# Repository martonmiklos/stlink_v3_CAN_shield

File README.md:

# STLink-v3 CAN breakout board

Replacement board for the MB1440 to expose the CAN bridge through an MCP2562-E/SN transciver to a DSUB connector

Drawn in Autodesk EAGLE 9.x

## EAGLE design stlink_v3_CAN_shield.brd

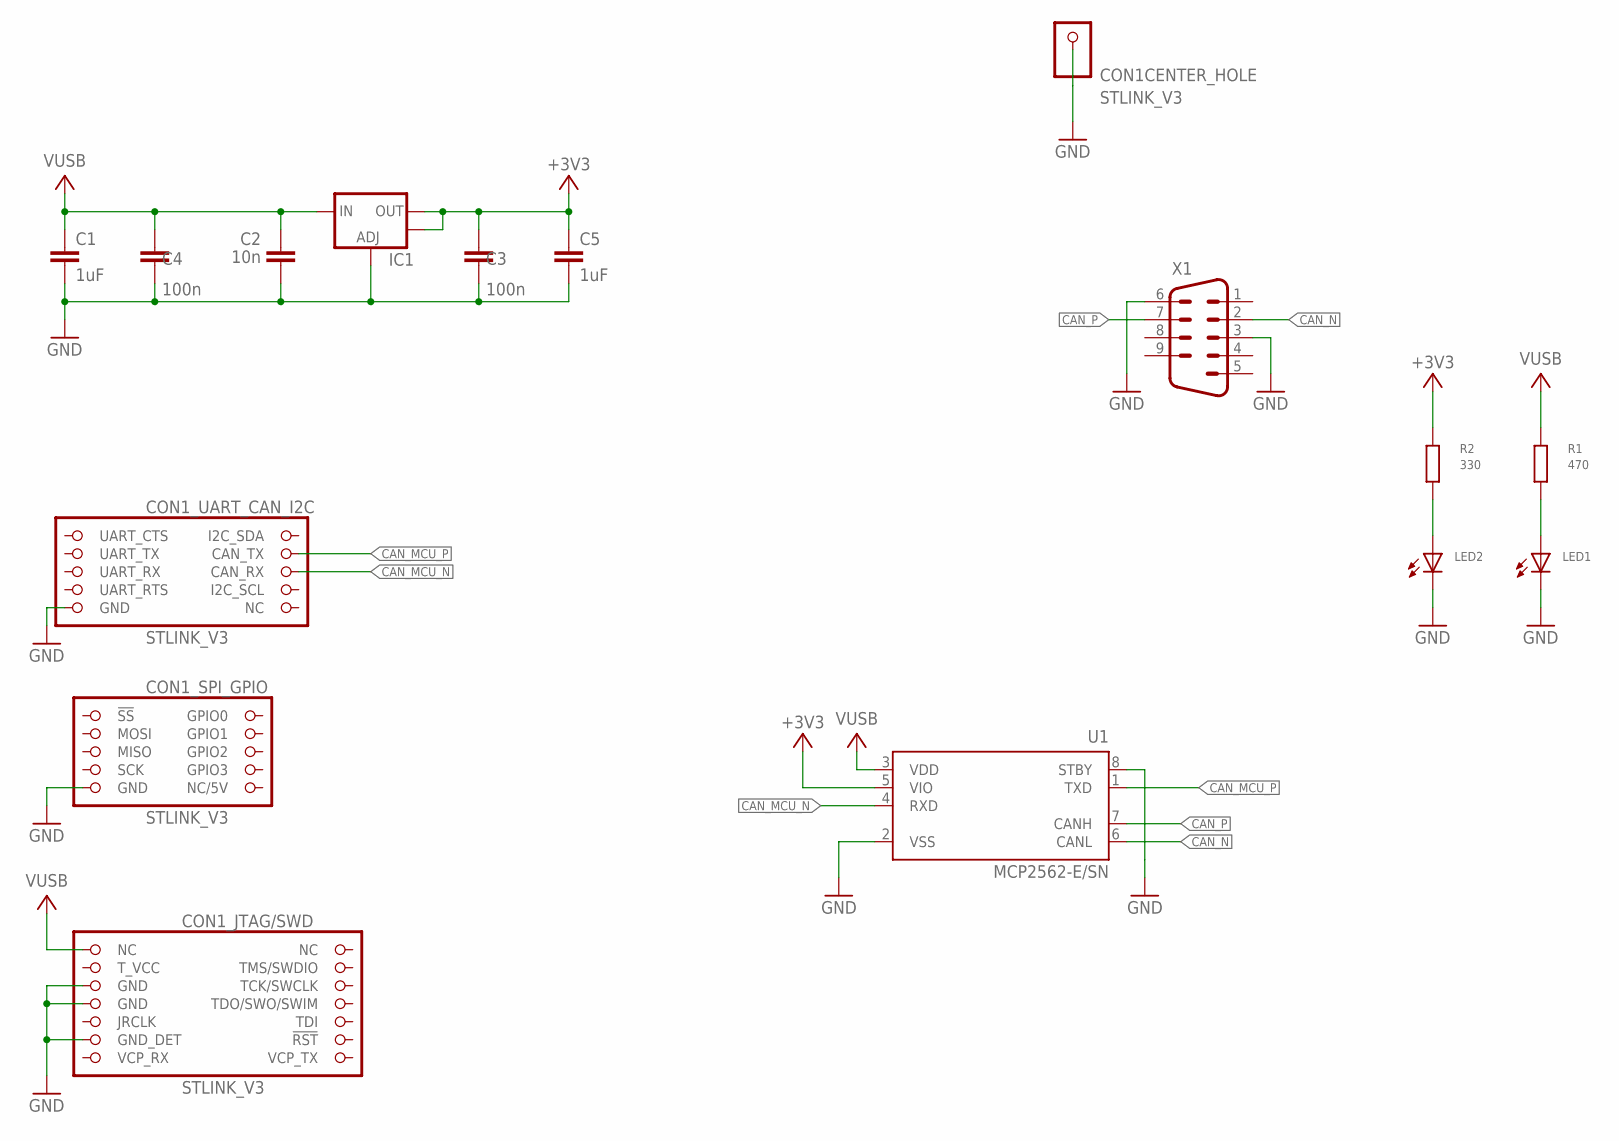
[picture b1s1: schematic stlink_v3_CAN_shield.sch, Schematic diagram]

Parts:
C1, C5: 1uF; C0603
C2: 10n; C0603
C3, C4: 100n; C0603
CON1: STLINK_V3; STLINKV3_HAT_NO_CONTOUR
IC1: V_REG_LM1117SOT223; SOT223
LED1, LED2: LED-0603; LED-603
R1: 470; R0603
R2: 330; R0603
U1: MCP2562-E/SN; SOIC127P600X175-8N
X1: M09H

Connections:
+3V3: C3.2, C5.1, IC1.2 (OUT), IC1.4 (OUT), R2.1, U1.5 (VIO)
CAN_MCU_N: CON1.UART_6 (CAN_RX), U1.4 (RXD)
CAN_MCU_P: CON1.UART_4 (CAN_TX), U1.1 (TXD)
CAN_N: U1.6 (CANL), X1.2
CAN_P: U1.7 (CANH), X1.7
GND: C1.2, C2.2, C3.1, C4.1, C5.2, CON1.CENTER (1), CON1.SPI_9 (GND), CON1.STDC_14_5 (GND), CON1.STDC_14_7 (GND), CON1.STDC_14_11 (GND_DET), CON1.UART_9 (GND), IC1.1 (ADJ), LED1.C, LED2.C, U1.2 (VSS), U1.8 (STBY), X1.3, X1.6
VIN_LED_R1: LED2.A, R2.2
VIN_LED_R2: LED1.A, R1.2
VUSB: C1.1, C2.1, C4.2, CON1.STDC_14_1 (NC), IC1.3 (IN), R1.1, U1.3 (VDD)

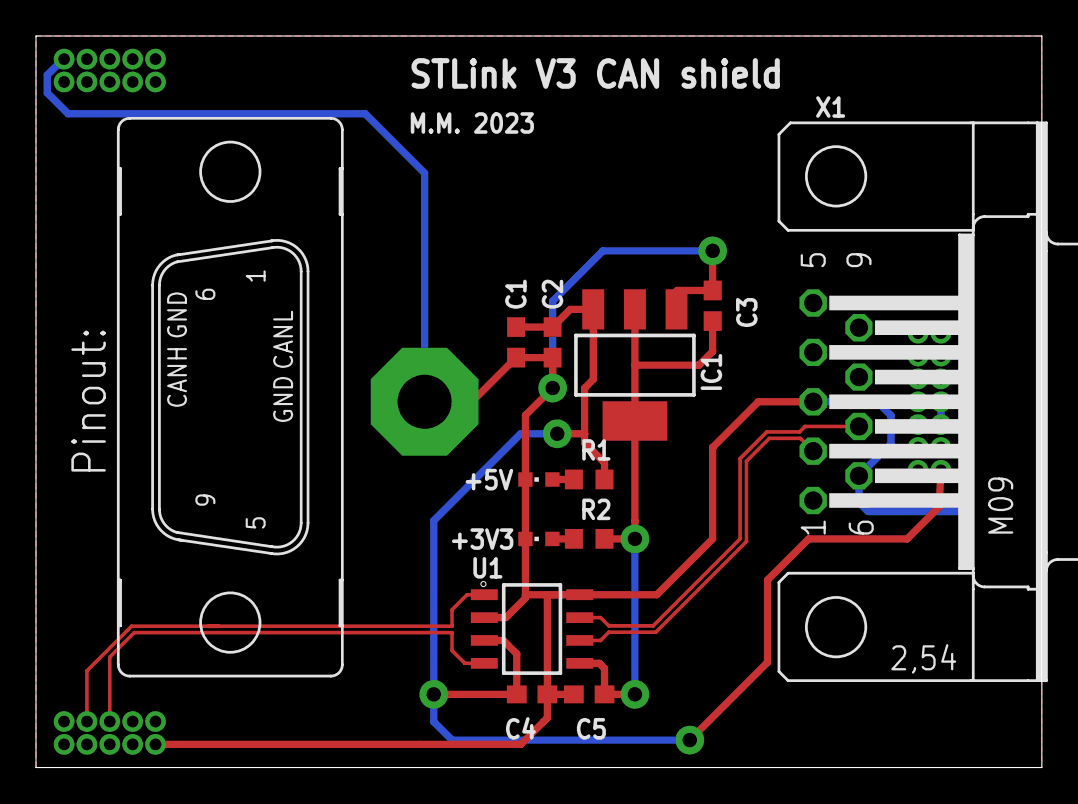
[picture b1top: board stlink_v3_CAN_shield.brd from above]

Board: 2 copper layers, 55.9 x 40.6 mm, 13 parts (0 on the bottom side), 9 nets.

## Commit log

2020-03-27 Repo init
2023-02-26 Update STLink footprint

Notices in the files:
parts and their libraries:
SparkFun: Licensing: CC v3.0 Share-Alike You are welcome to use this library for commercial purposes.
